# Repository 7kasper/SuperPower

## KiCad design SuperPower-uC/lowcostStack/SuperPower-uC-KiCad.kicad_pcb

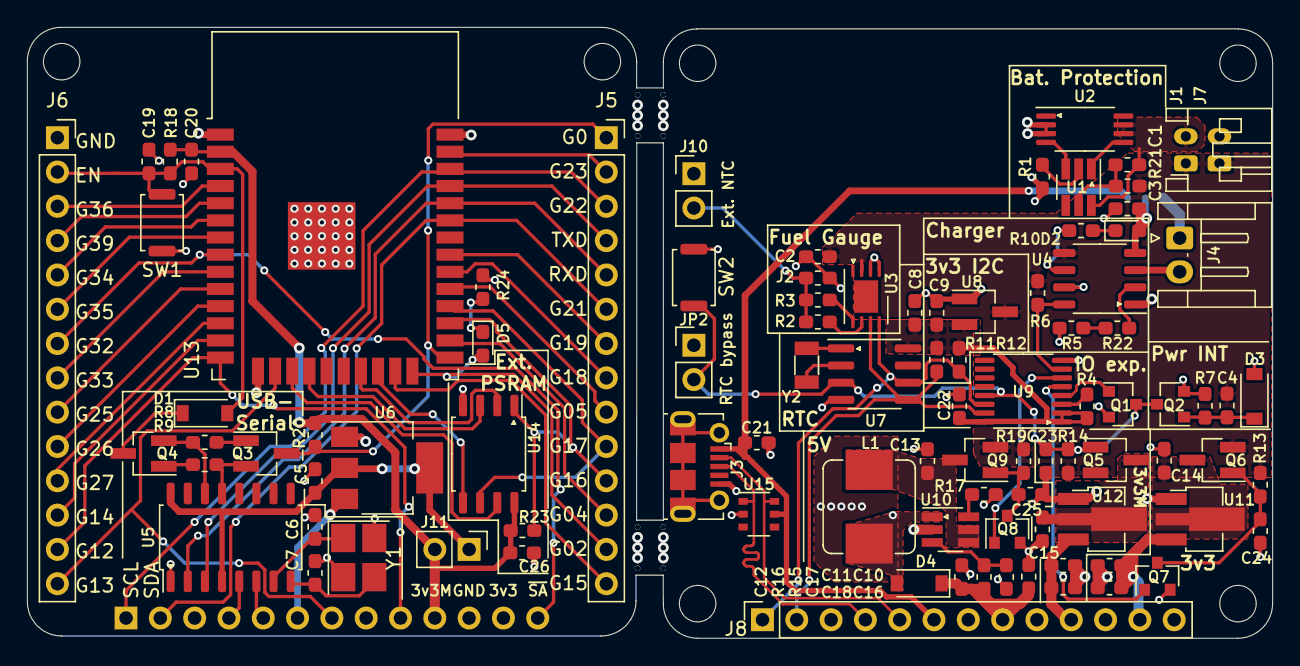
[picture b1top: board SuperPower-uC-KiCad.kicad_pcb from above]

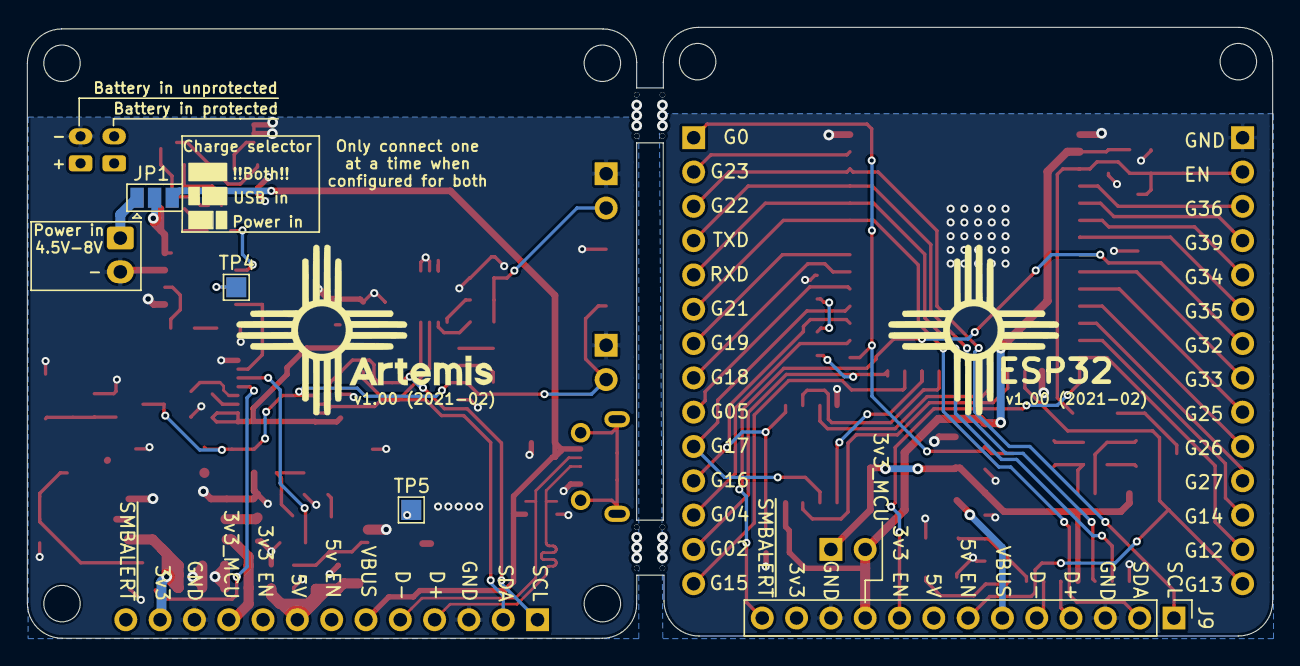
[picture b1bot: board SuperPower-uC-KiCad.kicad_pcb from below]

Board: 4 copper layers, 92.2 x 45.2 mm, 105 parts (4 on the bottom side), 87 nets.

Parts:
C1, C2, C8, C9, C14, C15, C20, C23, C24, C25, C26: 0.1µF; C_0603_1608Metric_Pad1.05x0.95mm_HandSolder
C3, C4, C5, C10, C11, C12, C13, C19, C21, C22: 1µF; C_0603_1608Metric_Pad1.05x0.95mm_HandSolder
C6, C7: 22pF; C_0603_1608Metric_Pad1.05x0.95mm_HandSolder
C16, C17, C18: 10µF; C_0603_1608Metric_Pad1.05x0.95mm_HandSolder
D1, D3, D4: B5819W; D_SOD-123
D2, D5: LED; LED_0603_1608Metric_Pad1.05x0.95mm_HandSolder
H1, H2, H3, H4, H5, H6: MountingHole; MountingHole_2.7mm_M2.5_ISO7380
J1: Battery connector; JST_PH_S2B-PH-K_1x02_P2.00mm_Horizontal
J2: Thermistor; R_0603_1608Metric_Pad1.05x0.95mm_HandSolder
J3: USB_B_Micro; USB_Micro-B_Molex-105017-0001
J4: Solar in; JST_EH_S2B-EH_1x02_P2.50mm_Horizontal
J5, J6: Conn_01x14_Female; PinSocket_1x14_P2.54mm_Vertical
J7: DNP; JST_PH_S2B-PH-K_1x02_P2.00mm_Horizontal
J8: regulator board; PinSocket_1x13_P2.54mm_Vertical
J9: MCU board; PinHeader_1x13_P2.54mm_Vertical
J10: External NTC; PinHeader_1x02_P2.54mm_Vertical
J11: DNP; PinHeader_1x02_P2.54mm_Vertical
JP1: CHRG_Jumper; SolderJumper-3_P1.3mm_Open_Pad1.0x1.5mm
JP2: RTC bypass; PinHeader_1x02_P2.54mm_Vertical
L1: 3.3u; L_Bourns_SRP7028A_7.3x6.6mm
Q1, Q2, Q7, Q8: 2N7002; SOT-23
Q3, Q4: S8050; SOT-23_Handsoldering
Q5, Q6, Q9: AO3401A; SOT-23_Handsoldering
R1, R5, R10, R22: 1k; R_0603_1608Metric_Pad1.05x0.95mm_HandSolder
R2, R24: 100; R_0603_1608Metric_Pad1.05x0.95mm_HandSolder
R3, R8, R9, R11, R12, R18, R20, R23: 10k; R_0603_1608Metric_Pad1.05x0.95mm_HandSolder
R4, R6, R16: 180k; R_0603_1608Metric_Pad1.05x0.95mm_HandSolder
R7, R13, R14, R19: 1M; R_0603_1608Metric_Pad1.05x0.95mm_HandSolder
R15, R17: 22k; R_0603_1608Metric_Pad1.05x0.95mm_HandSolder
R21: 330; R_0603_1608Metric_Pad1.05x0.95mm_HandSolder
SW1, SW2: DNP; SW_Push_SPST_NO_Alps_SKRK
TP4, TP5: TestPoint; TestPoint_Pad_1.5x1.5mm
U1: AP9101CK6-ADTRG1; SOT-23-6_Handsoldering
U2: FS8205A; TSSOP-8_4.4x3mm_P0.65mm
U3: LC709203FQH; WDFN-8-1EP_4x3mm_P0.65mm_EP2.4x1.8mm
U4: TP4056; SOP-8_3.9x4.9mm_P1.27mm
U5: CH340G; SOP-16_4.55x10.3mm_P1.27mm
U6: AMS1117-3.3; SOT-223-3_TabPin2
U7: PCF8563T; SOIC-8_3.9x4.9mm_P1.27mm
U8: XC6206P332MR; SOT-23_Handsoldering
U9: TCA6408A; TSSOP-16_4.4x5mm_P0.65mm
U10: FP6291LR; SOT-23-6_Handsoldering
U11, U12: ME6210A33P; SOT-89-3_Handsoldering
U13: ESP32-WROOM32; ESP32-WROOM-32
U14: W25Q32JVSS; SOIC-8_5.23x5.23mm_P1.27mm
U15: IP4220CZ6; TSOP-6_1.65x3.05mm_P0.95mm
Y1: 12MHZ; Crystal_SMD_3225-4Pin_3.2x2.5mm_HandSoldering
Y2: 32.768KHz; Crystal_SMD_3215-2Pin_3.2x1.5mm

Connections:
3v3_EN: Q7.1, U9.5
5V_EN: Q8.1, U9.6
/3v3: C10.1, C16.1, J8.12, U11.3
/3v3_MCU_1: C11.1, C18.1, J8.10, U12.3
/3v3_MCU_2: C20.2, C26.2, J9.10, J11.2, R18.1, R20.1, R23.1, U13.2, U14.8
/5v: C12.1, C17.1, D4.1, J8.8, R16.1
/Battery Module/BAT-: C1.2, J1.2, U1.6, U2.6, U2.7
/Battery Module/VBAT: C2.2, C4.1, J1.1, J7.1, Q5.2, Q6.2, Q9.2, R6.1, R13.2, R14.2, R19.2, R21.1, U3.3, U4.5, U8.3
/Charger I/O/VCHARGE: C3.1, D2.2, JP1.2, U4.4
/Charging Module/3v3_I2C: C8.2, C9.2, C22.2, R4.1, R11.2, R12.2, U7.8, U8.2, U9.1, U9.2, U9.16
/Charging Module/STDBY: R10.2, U4.6
/D1+: J3.3, J8.4, U15.1
/D1-: J3.2, J8.5, U15.6
/D2+: J9.4, U5.5
/D2-: J9.5, U5.6
/EN_3v3: J6.13, J9.9, U13.14
/EN_5v: J6.14, J9.7, U13.16
/MCU Module/3v3_UART: C5.2, J11.1, U5.4, U5.16, U6.2
/MCU Module/IO0: J5.1, Q3.3, R20.2, U13.25
/MCU Module/IO2: D5.2, J5.13, U13.24
/MCU Module/IO4: J5.12, U13.26
/MCU Module/IO5: J5.9, U13.29
/MCU Module/IO14: J6.12, U13.13
/MCU Module/IO15: J5.14, U13.23
/MCU Module/IO16: J5.11, R23.2, U13.27, U14.1
/MCU Module/IO17: J5.10, U13.28, U14.6
/MCU Module/IO18: J5.8, U13.30
/MCU Module/IO19: J5.7, U13.31
/MCU Module/IO23: J5.2, U13.37
/MCU Module/IO25: J6.9, U13.10
/MCU Module/IO26: J6.10, U13.11
/MCU Module/IO27: J6.11, U13.12
/MCU Module/IO33: J6.8, U13.9
/MCU Module/IO34: J6.5, U13.6
/MCU Module/IO35: J6.6, U13.7
/MCU Module/IO36: J6.3, U13.4
/MCU Module/IO39: J6.4, U13.5
/MCU Module/PSRAM_SD0: U13.21, U14.2
/MCU Module/PSRAM_SD1: U13.22, U14.5
/MCU Module/PSRAM_SD2: U13.17, U14.7
/MCU Module/PSRAM_SD3: U13.18, U14.3
/MCU Module/RST: C19.1, D1.2, J6.2, R18.2, SW1.1, U13.3
/MCU Module/RX: J5.5, U5.2, U13.34
/MCU Module/TX: J5.4, U5.3, U13.35
/SCL_1: J8.1, R12.1, U3.8, U7.6, U9.14
/SCL_2: J5.3, J9.1, U13.36
/SDA_1: J8.2, R11.1, U3.7, U7.5, U9.15
/SDA_2: J5.6, J9.2, U13.33
/VBUS_1: C21.1, J3.1, J8.6, JP1.3, U15.5
/VBUS_2: J9.6, U6.3
/~SMBALERT: J6.7, J9.13, U13.8
CH_DIS: R6.2, U4.8, U9.7
GND: C2.1, C3.2, C5.1, C6.2, C7.2, C8.1, C9.1, C10.2, C11.2, C12.2, C13.2, C14.2, C15.2, C16.2, C17.2, C18.2, C19.2, C20.1, C21.2, C22.1, C23.1, C24.2, C25.2, C26.1, D3.2, J2.2, J3.5, J4.2, J6.1, J7.2, J8.3, J8.11, J9.3, J9.11, J10.1, JP2.1, Q1.2, Q2.2, Q7.2, Q8.2, R1.2, R5.2, R7.1, R15.2, R17.2, R24.2, SW1.2, SW2.2, U2.2, U2.3, U3.1, U3.2, U4.1, U4.3, U5.1, U6.1, U7.4, U8.1, U9.8, U10.2, U11.1, U12.1, U13.1, U13.15, U13.38, U13.39, U14.4, U15.2, Y1.2, Y1.4
INT_IO: C23.2, JP2.2, Q1.3, Q2.3, Q5.1, R14.1, SW2.1, U7.3, U9.13
unnamed: C1.1, R21.2, U1.5
unnamed: C4.2, D3.1, Q2.1, R7.2
unnamed: C6.1, U5.7, Y1.1
unnamed: C7.1, U5.8, Y1.3
unnamed: C13.1, L1.1, Q9.3, U10.4, U10.5
unnamed: C14.1, Q6.3, U11.2
unnamed: C15.1, Q5.3, U12.2
unnamed: C24.1, Q6.1, Q7.3, R13.1
unnamed: C25.1, Q8.3, Q9.1, R19.1
unnamed: D1.1, Q4.3
unnamed: D2.1, R10.1
unnamed: D4.2, L1.2, TP5.1, U10.1
unnamed: D5.1, R24.1
unnamed: J4.1, JP1.1
unnamed: J2.1, J10.2, R2.2, R3.2
unnamed: Q1.1, U9.4
unnamed: Q3.1, R8.1
unnamed: Q3.2, R9.2, U5.13
unnamed: Q4.1, R9.1
unnamed: Q4.2, R8.2, U5.14
unnamed: R1.1, U1.2
unnamed: R2.1, U3.6
unnamed: R3.1, U3.5
unnamed: R4.2, U9.3
unnamed: R15.1, R16.2, U10.3
unnamed: R17.1, U10.6
unnamed: R22.1, U4.2
unnamed: R5.1, R22.2
unnamed: TP4.1, U4.7
unnamed: U1.1, U2.5
unnamed: U1.3, U2.4
unnamed: U7.1, Y2.2
unnamed: U7.2, Y2.1
